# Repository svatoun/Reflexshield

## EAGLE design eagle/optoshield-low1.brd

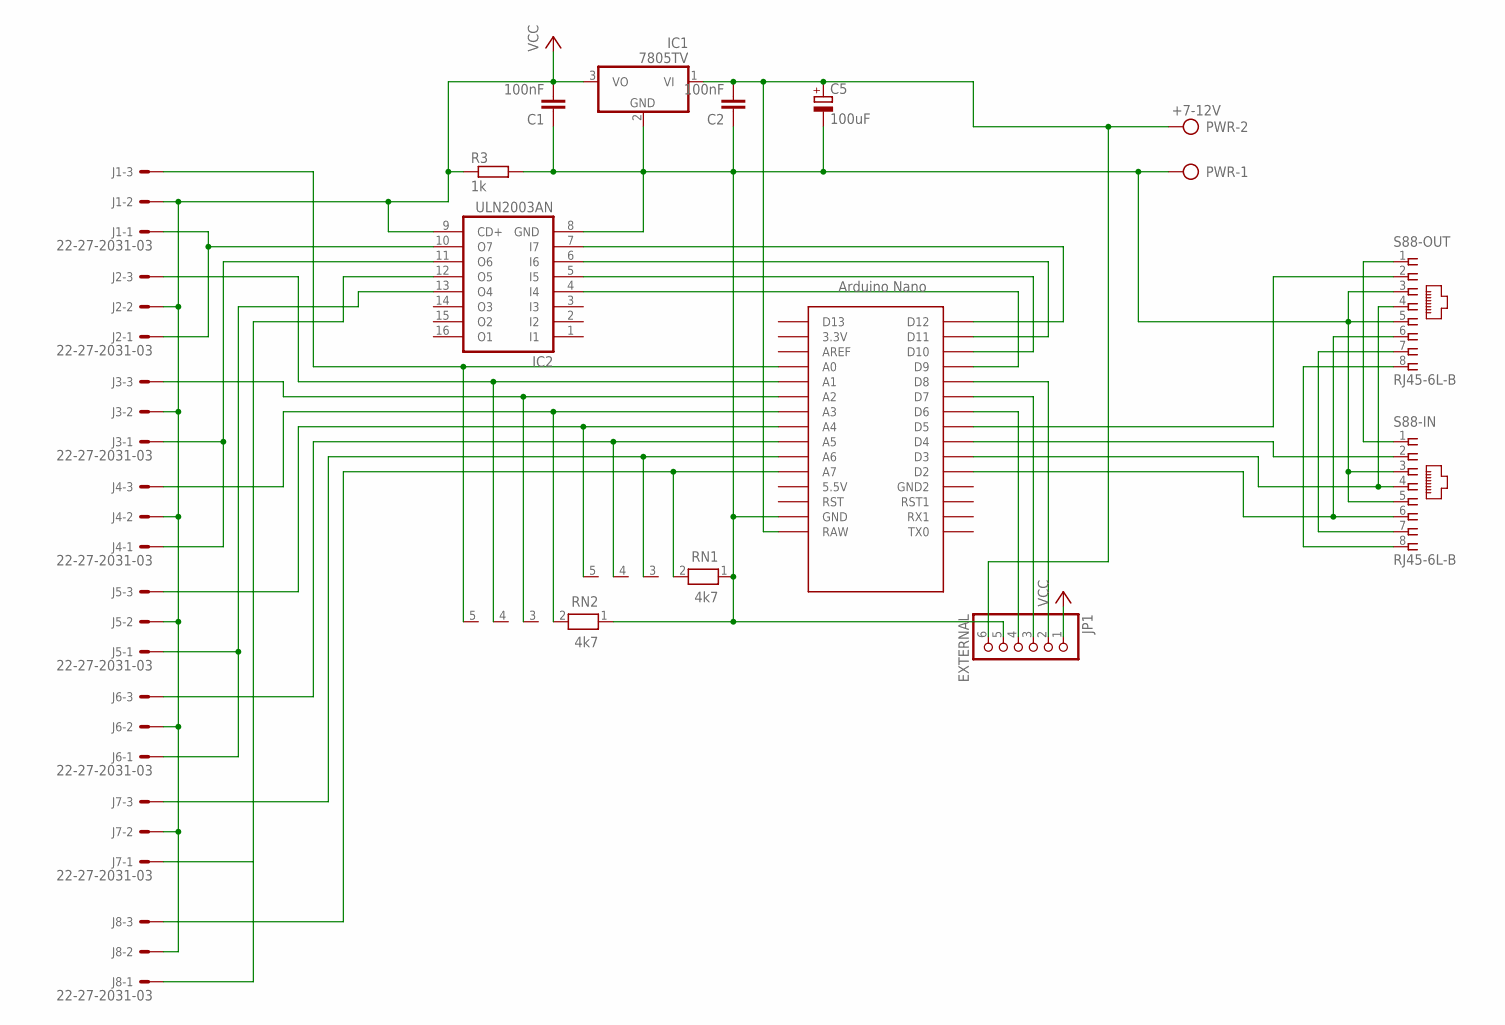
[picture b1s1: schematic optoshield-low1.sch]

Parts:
C1, C2: 100nF; C025-025X050
C5: 100uF; E3,5-10
IC1: 7805TV; TO220V
IC2: ULN2003AN; DIL16
J1, J2, J3, J4, J5, J6, J7, J8: 22-27-2031-03; 6410-03
JP1: EXTERNAL; 1X06
PWR: +7-12V; AK500/2
R3: 1k; 0207/10
RN1, RN2: 4k7; RN-5
S88-IN, S88-OUT: RJ45-6L-B; RJ45-NO-SHIELD
U$1: NANO

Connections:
GND: C1.1, C2.1, C5.-, IC1.2 (GND), IC2.8 (GND), JP1.5, PWR.1, R3.2, RN1.1, RN2.1, S88-IN.3, S88-IN.5, S88-OUT.3, S88-OUT.5, U$1.GND
unnamed: C2.2, C5.+, IC1.1 (VI), JP1.6, PWR.2, U$1.RAW
unnamed: S88-IN.1, S88-OUT.1
unnamed: JP1.2, U$1.D8
unnamed: J1.3, RN2.5, U$1.A0
unnamed: J4.3, RN2.2, U$1.A3
unnamed: J5.3, RN1.5, U$1.A4
unnamed: J2.3, RN2.4, U$1.A1
unnamed: J3.3, RN2.3, U$1.A2
unnamed: J6.3, RN1.4, U$1.A5
unnamed: J7.3, RN1.3, U$1.A6
unnamed: J8.3, RN1.2, U$1.A7
unnamed: JP1.3, U$1.D7
unnamed: S88-IN.8, S88-OUT.8
unnamed: S88-IN.6, S88-OUT.6, U$1.D2
unnamed: IC2.7 (I7), U$1.D12
unnamed: S88-IN.7, S88-OUT.7
unnamed: S88-IN.4, S88-OUT.4, U$1.D3
unnamed: S88-IN.2, U$1.D4
unnamed: IC2.12 (O5), J7.1, J8.1
unnamed: S88-OUT.2, U$1.D5
unnamed: IC2.6 (I6), U$1.D11
unnamed: IC2.5 (I5), U$1.D10
unnamed: IC2.4 (I4), U$1.D9
unnamed: JP1.4, U$1.D6
unnamed: IC2.10 (O7), J1.1, J2.1
unnamed: IC2.11 (O6), J3.1, J4.1
unnamed: IC2.13 (O4), J5.1, J6.1
VCC: C1.2, IC1.3 (VO), IC2.9 (CD+), J1.2, J2.2, J3.2, J4.2, J5.2, J6.2, J7.2, J8.2, JP1.1, R3.1

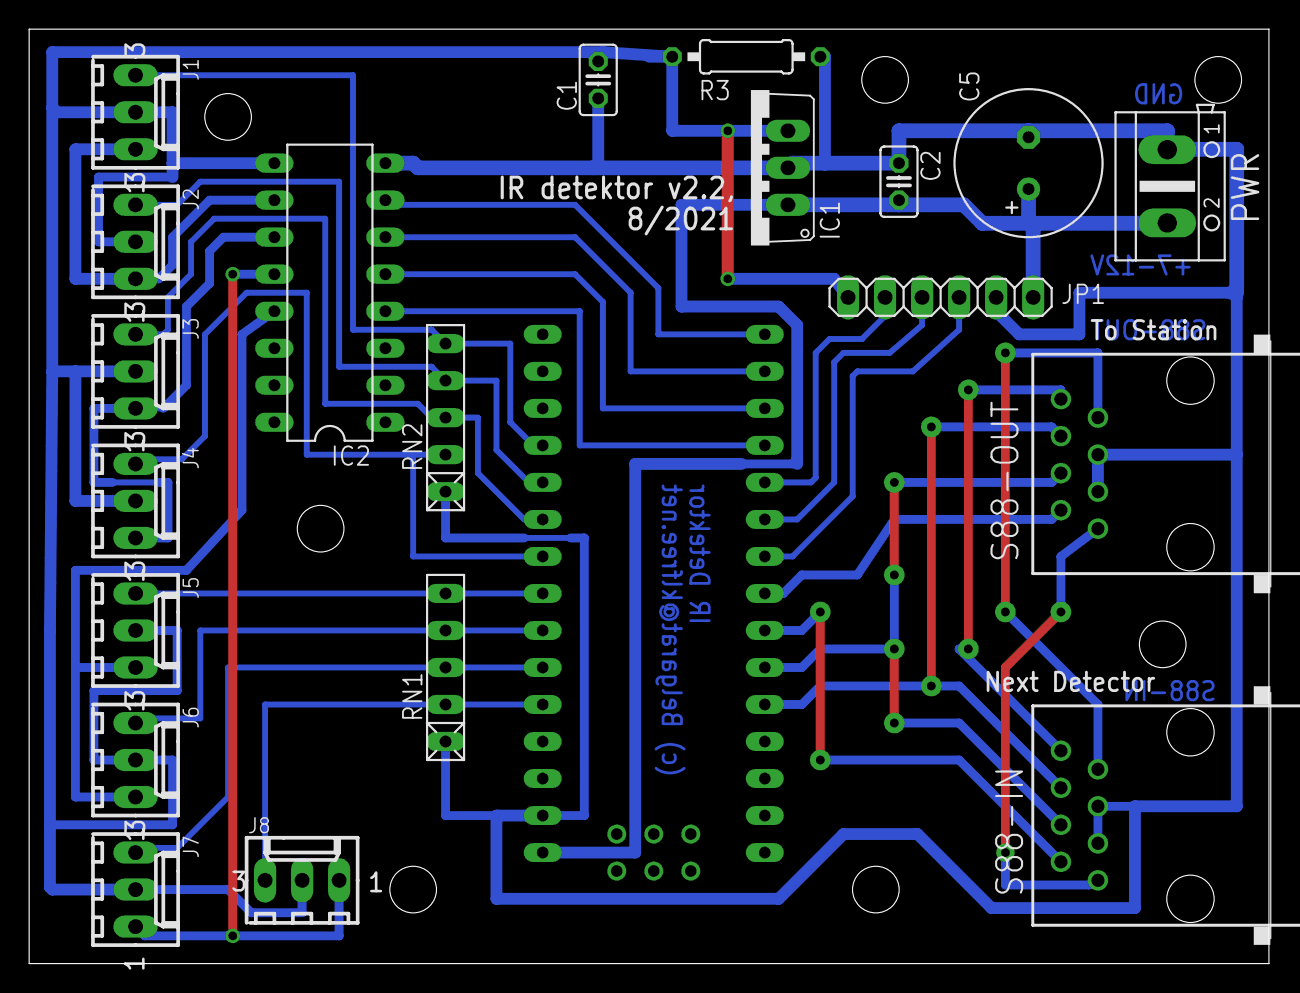
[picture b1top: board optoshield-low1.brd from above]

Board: 2 copper layers, 85.1 x 64.1 mm, 21 parts (0 on the bottom side), 29 nets.

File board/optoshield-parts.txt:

Partlist

Exported from optoshield3.sch at 21.08.17 23:17

EAGLE Version 6.6.0 Copyright (c) 1988-2014 CadSoft

Assembly variant: 

Part     Value          Device          Package        Library             Sheet

C1       100nF          C-EU025-025X050 C025-025X050   rcl                 1
C2       100nF          C-EU025-025X050 C025-025X050   rcl                 1
C5       100uF          CPOL-EUE3.5-10  E3,5-10        resistor            1
IC1      7805TV         7805TV          TO220V         linear              1
J1       22-27-2031-03  22-27-2031-03   6410-03        con-molex           1
J2       22-27-2031-03  22-27-2031-03   6410-03        con-molex           1
J3       22-27-2031-03  22-27-2031-03   6410-03        con-molex           1
J4       22-27-2031-03  22-27-2031-03   6410-03        con-molex           1
J5       22-27-2031-03  22-27-2031-03   6410-03        con-molex           1
J6       22-27-2031-03  22-27-2031-03   6410-03        con-molex           1
J7       22-27-2031-03  22-27-2031-03   6410-03        con-molex           1
J8       22-27-2031-03  22-27-2031-03   6410-03        con-molex           1
JP1      CTRL           PINHD-1X6       1X06           pinhead             1
PWR      +5V            AK500/2         AK500/2        con-ptr500          1
R1       510R           R-EU_0207/10    0207/10        rcl                 1
R2       4k7            R-EU_0207/10    0207/10        rcl                 1
R3       1k             R-EU_0207/10    0207/10        resistor            1
RN1      4k7            RN04            RN-5           resistor-net        1
RN2      4k7            RN04            RN-5           resistor-net        1
S88-IN   RJ45-6L-B      RJ45-6L-B       RJ45-NO-SHIELD con-tycoelectronics 1
S88-OUT  RJ45-6L-B      RJ45-6L-B       RJ45-NO-SHIELD con-tycoelectronics 1
T1       BC337          BC337           TO92           transistor          1
U$1      NANO           NANO            NANO           Arduino-clone       1

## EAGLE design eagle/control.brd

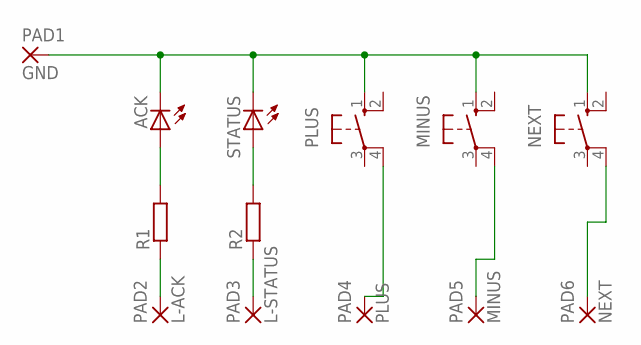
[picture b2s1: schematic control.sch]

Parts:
ACK: LED3MM
MINUS: 10-XX; B3F-10XX
NEXT: 10-XX; B3F-10XX
PAD1: GND; SMD1,27-2,54
PAD2: L-ACK; SMD1,27-2,54
PAD3: L-STATUS; SMD1,27-2,54
PAD4: PLUS; SMD1,27-2,54
PAD5: MINUS; SMD1,27-2,54
PAD6: NEXT; SMD1,27-2,54
PLUS: 10-XX; B3F-10XX
R1, R2: R-EU_R0805; R0805
STATUS: LED3MM

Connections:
unnamed: PAD2.1, R1.1
unnamed: PAD3.1, R2.1
unnamed: ACK.A, R1.2
unnamed: R2.2, STATUS.A
unnamed: PAD4.1, PLUS.4 (P1)
unnamed: MINUS.4 (P1), PAD5.1
unnamed: NEXT.4 (P1), PAD6.1
unnamed: ACK.K (C), MINUS.1 (S), NEXT.1 (S), PAD1.1, PLUS.1 (S), STATUS.K (C)

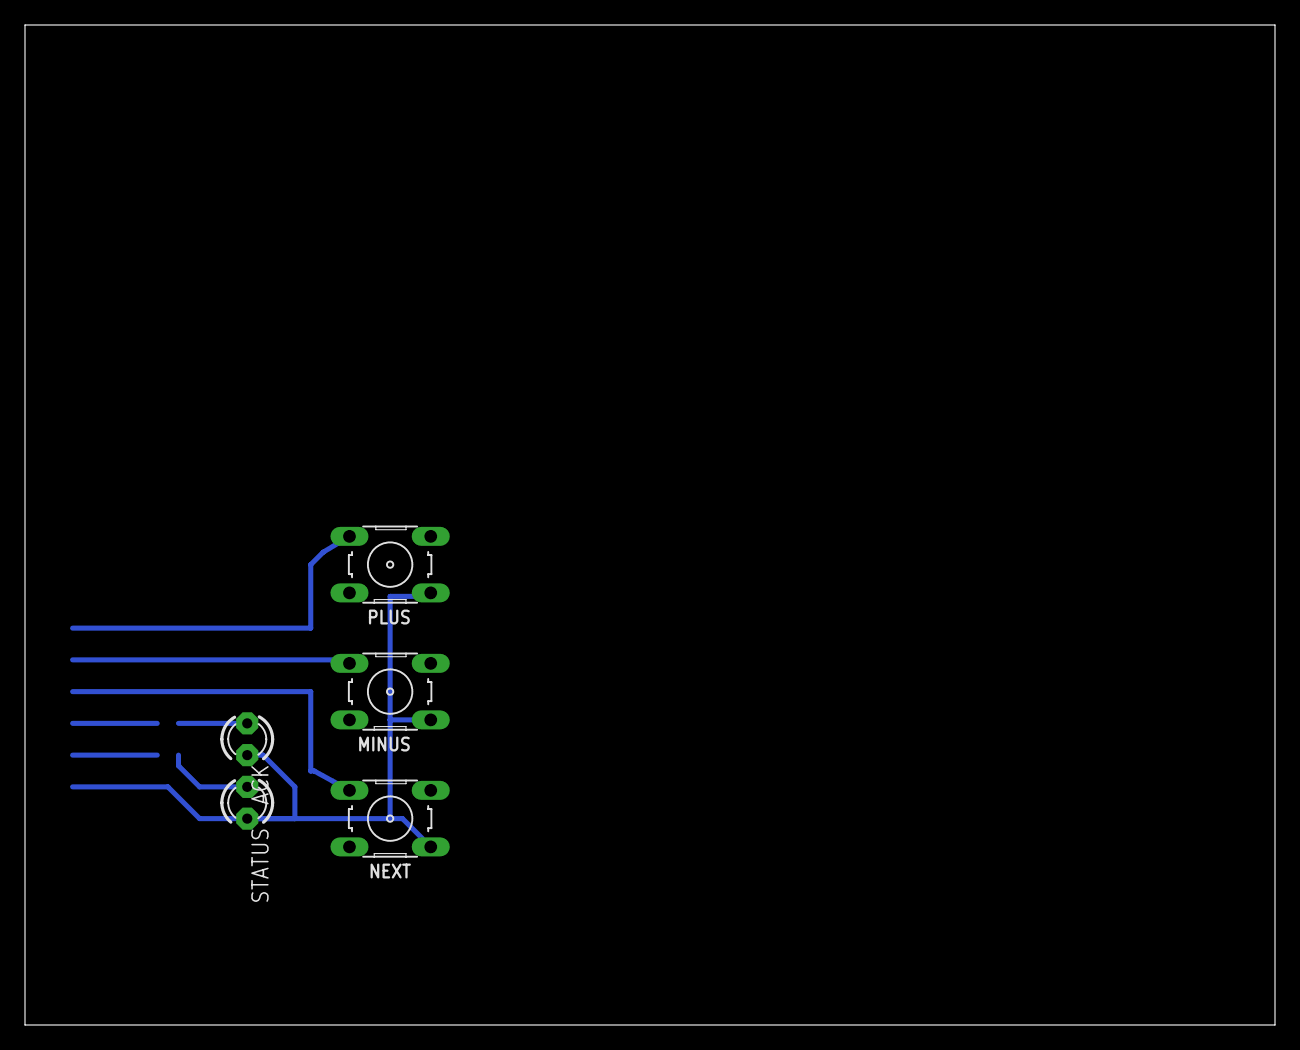
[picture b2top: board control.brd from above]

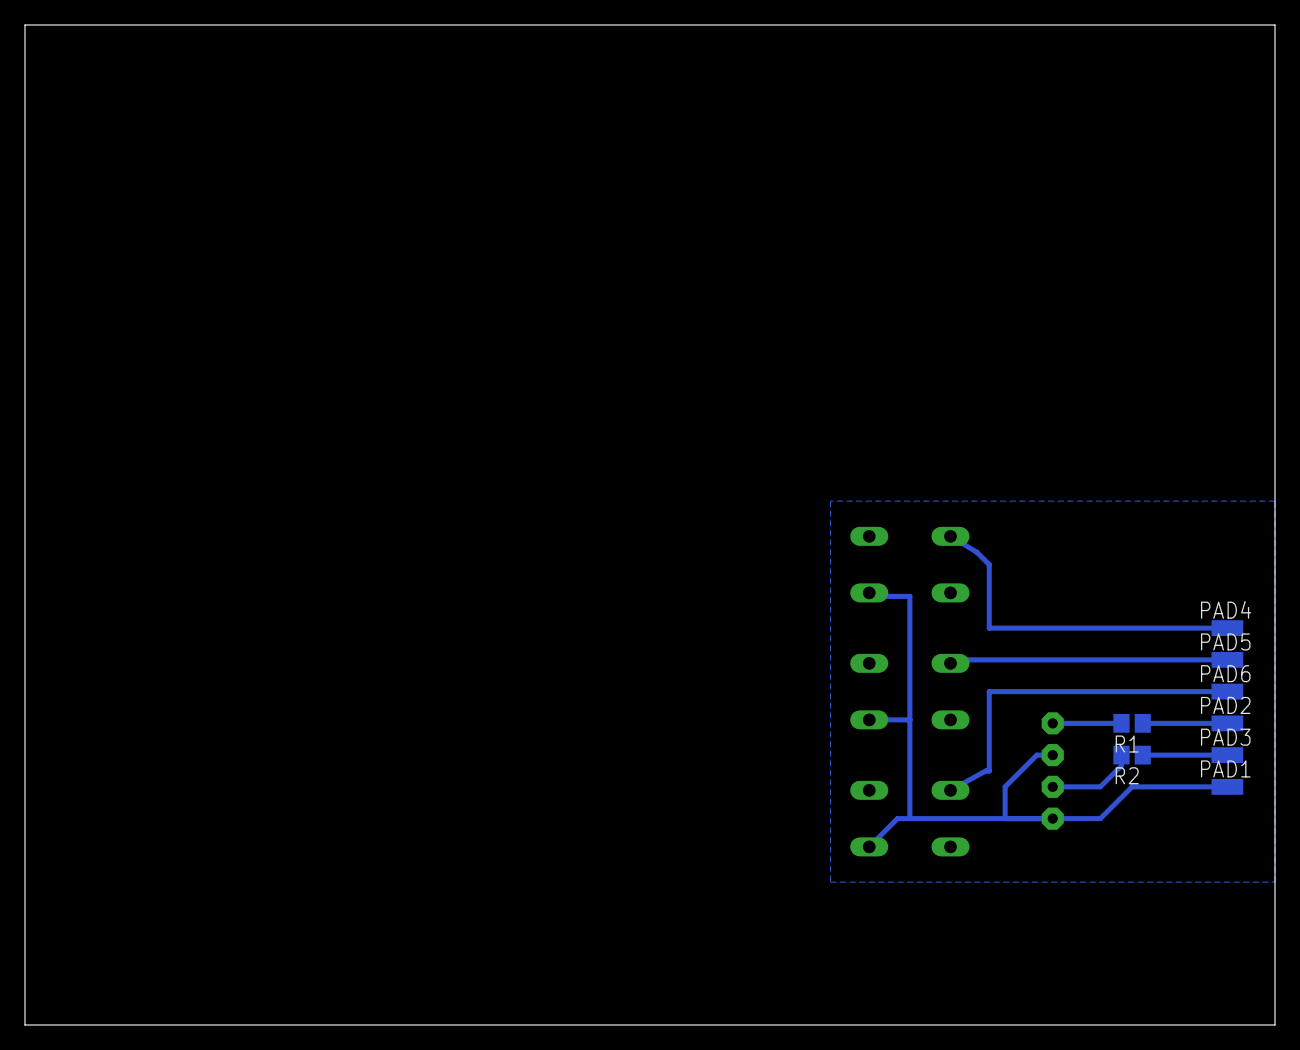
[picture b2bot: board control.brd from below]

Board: 2 copper layers, 100.0 x 80.0 mm, 13 parts (8 on the bottom side), 8 nets.

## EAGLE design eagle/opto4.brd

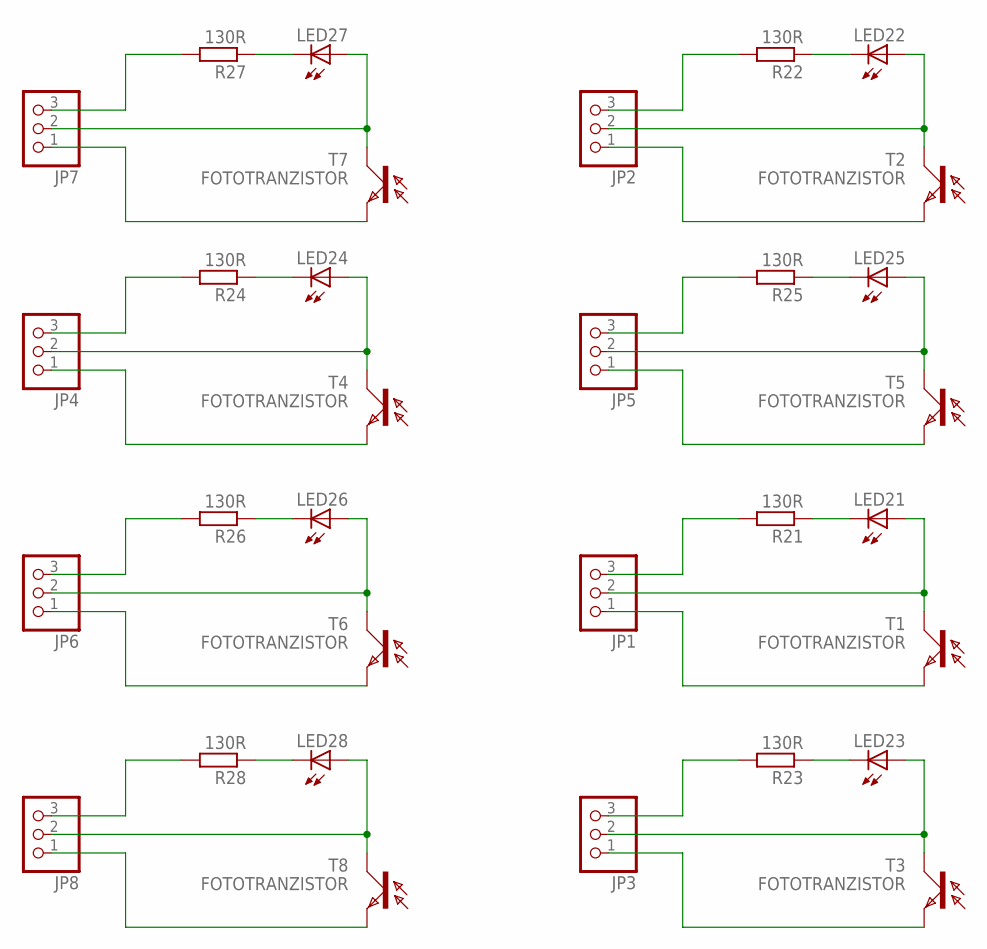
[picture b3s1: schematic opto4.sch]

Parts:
JP1, JP2, JP3, JP4, JP5, JP6, JP7, JP8: PINHD-1X3/90; 1X03/90
LED21, LED22, LED23, LED24, LED25, LED26, LED27, LED28: LED3MM
R21, R22, R23, R24, R25, R26, R27, R28: 130R; R1206
T1, T2, T3, T4, T5, T6, T7, T8: FOTOTRANZISTOR; BPX81

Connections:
unnamed: LED25.K (C), R25.1
unnamed: JP1.3, R21.2
unnamed: JP1.2, LED21.A, T1.C
unnamed: JP1.1, T1.E
unnamed: LED21.K (C), R21.1
unnamed: JP2.3, R22.2
unnamed: JP2.2, LED22.A, T2.C
unnamed: JP2.1, T2.E
unnamed: LED22.K (C), R22.1
unnamed: JP3.3, R23.2
unnamed: JP3.2, LED23.A, T3.C
unnamed: JP3.1, T3.E
unnamed: LED23.K (C), R23.1
unnamed: JP4.3, R24.2
unnamed: JP4.2, LED24.A, T4.C
unnamed: JP5.3, R25.2
unnamed: JP4.1, T4.E
unnamed: JP5.2, LED25.A, T5.C
unnamed: JP5.1, T5.E
unnamed: LED24.K (C), R24.1
unnamed: JP6.3, R26.2
unnamed: JP6.2, LED26.A, T6.C
unnamed: JP6.1, T6.E
unnamed: LED26.K (C), R26.1
unnamed: JP7.3, R27.2
unnamed: JP7.2, LED27.A, T7.C
unnamed: JP7.1, T7.E
unnamed: LED27.K (C), R27.1
unnamed: JP8.3, R28.2
unnamed: JP8.2, LED28.A, T8.C
unnamed: JP8.1, T8.E
unnamed: LED28.K (C), R28.1

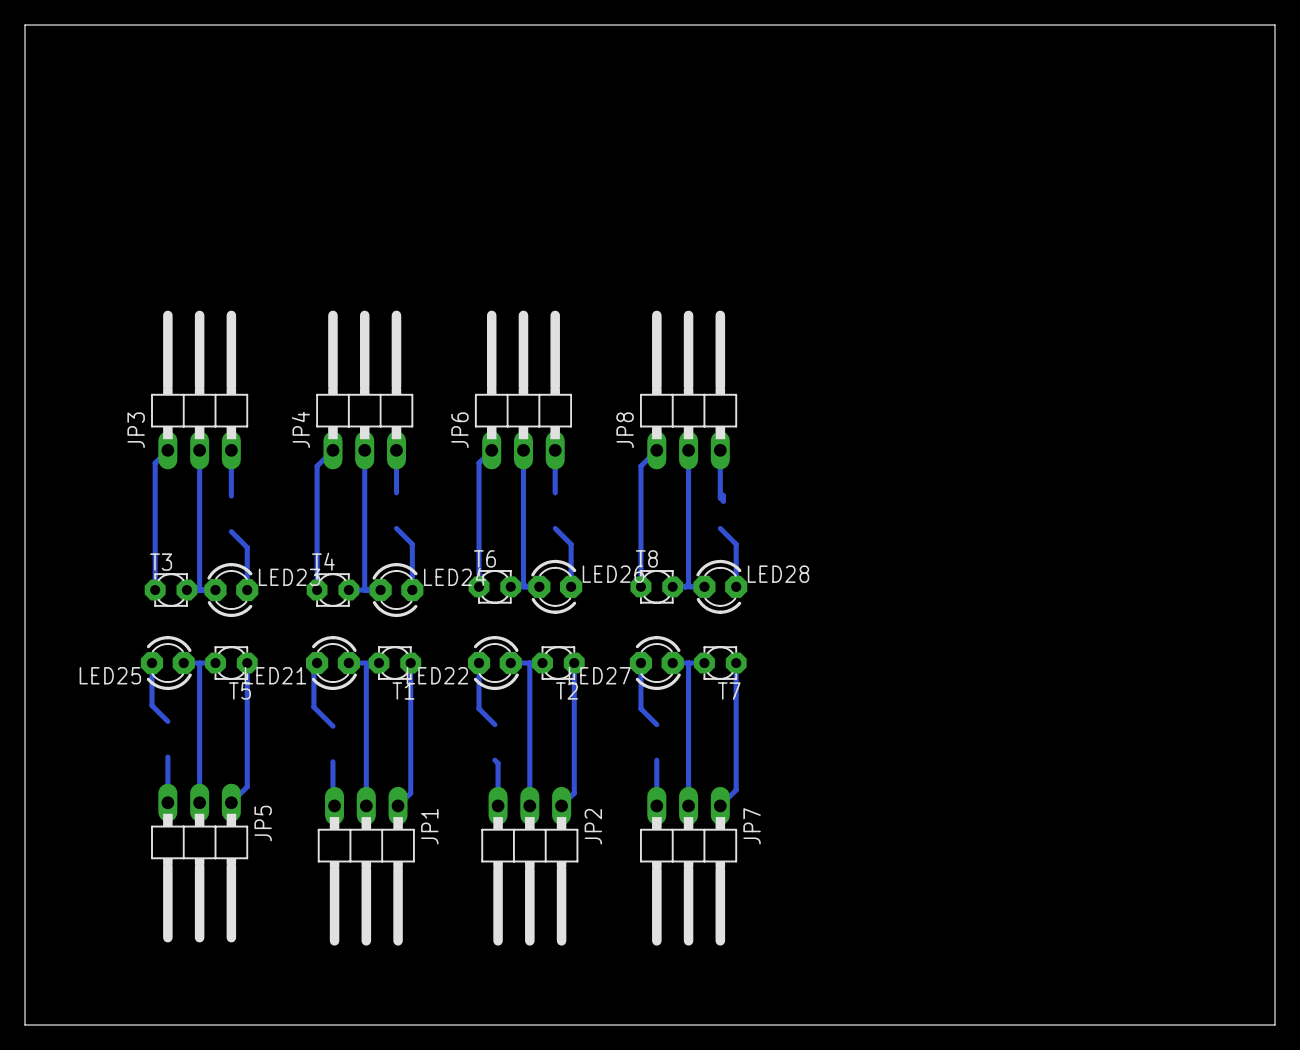
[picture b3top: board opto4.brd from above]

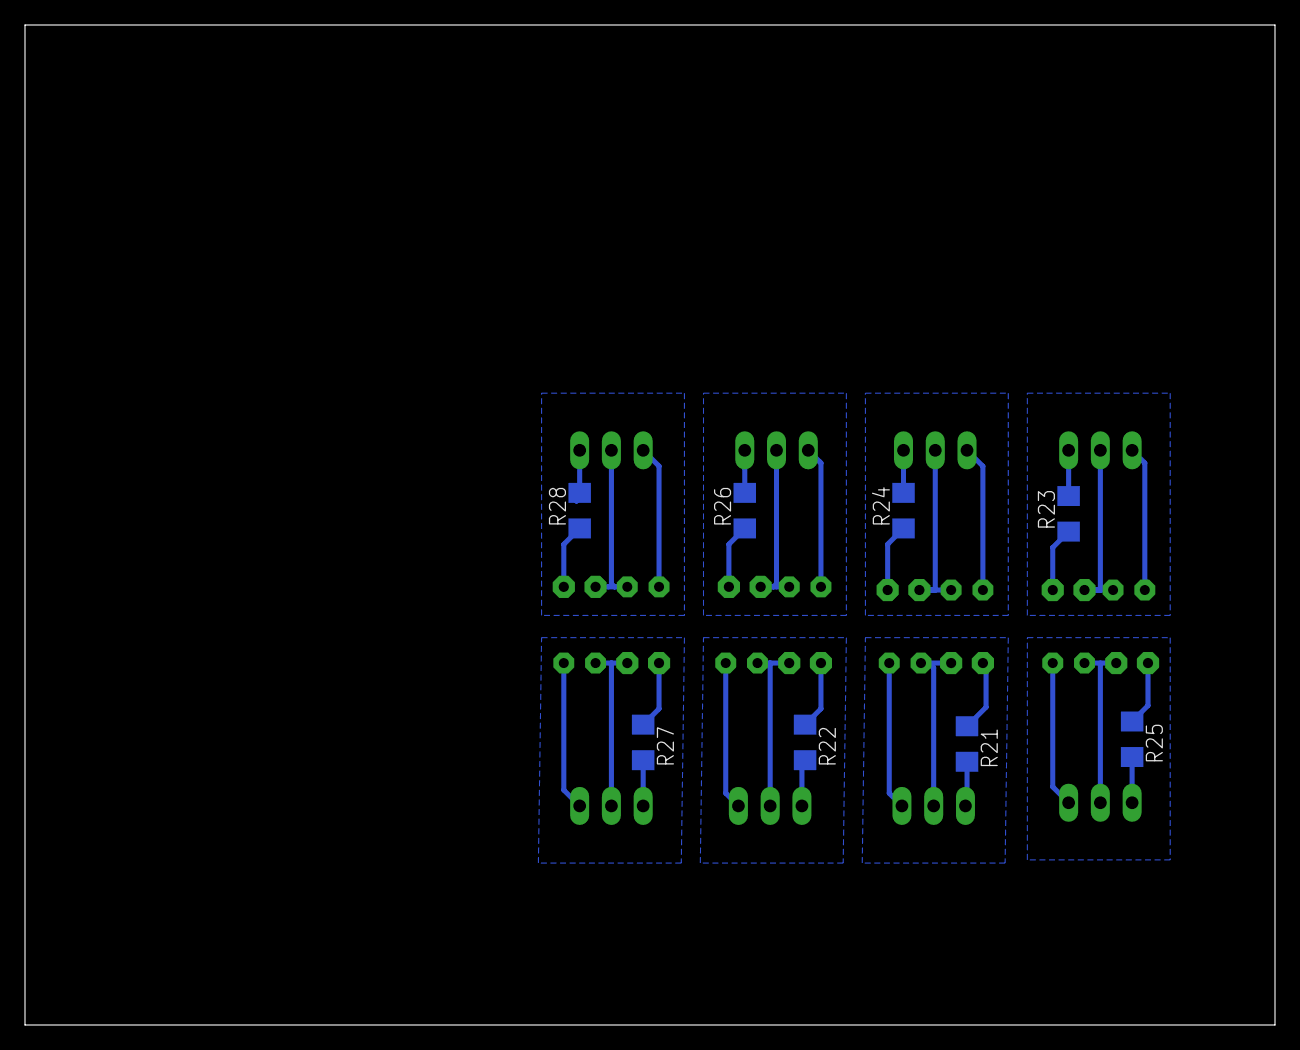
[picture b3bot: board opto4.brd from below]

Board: 2 copper layers, 100.0 x 80.0 mm, 32 parts (8 on the bottom side), 32 nets.

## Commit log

2017-08-22 Initial sketch and board files
2018-08-19 Cleaned up
2019-08-12 Pridany terminal
2020-08-03 Separated functional parts into independent sources.
2020-08-18 Neco nepovedeneho
2021-07-20 Relays added.
2021-08-22 Pridane mereni jednoho senzoru.
2021-09-17 Fixes
2021-09-18 Dokumentace
2021-09-18 Vzdy se scanuje 8 senzoru. Oprava chyb.
2021-09-23 Zruseny stary design eagle
2021-09-23 Update verze.
2021-09-28 DPS v3.0
